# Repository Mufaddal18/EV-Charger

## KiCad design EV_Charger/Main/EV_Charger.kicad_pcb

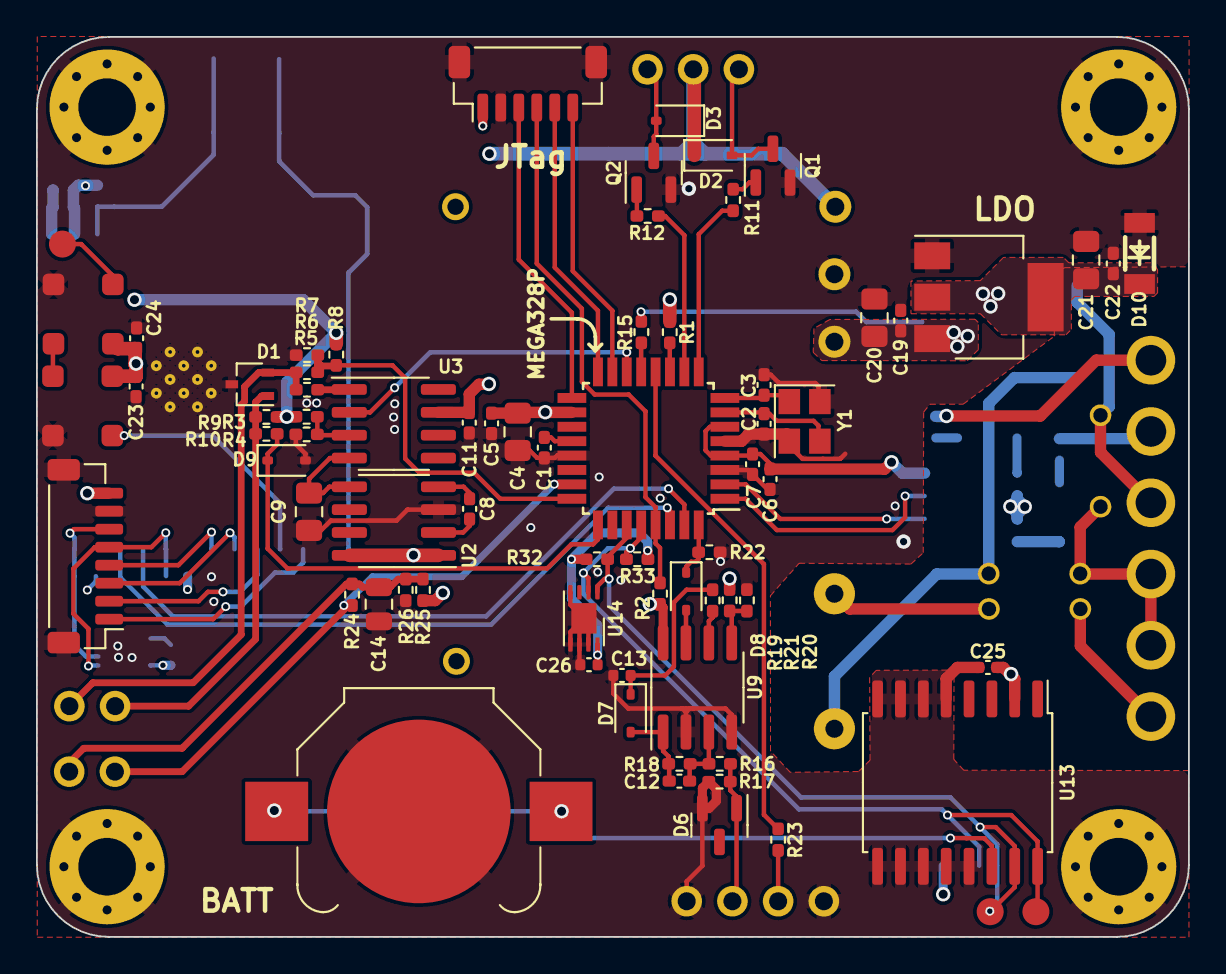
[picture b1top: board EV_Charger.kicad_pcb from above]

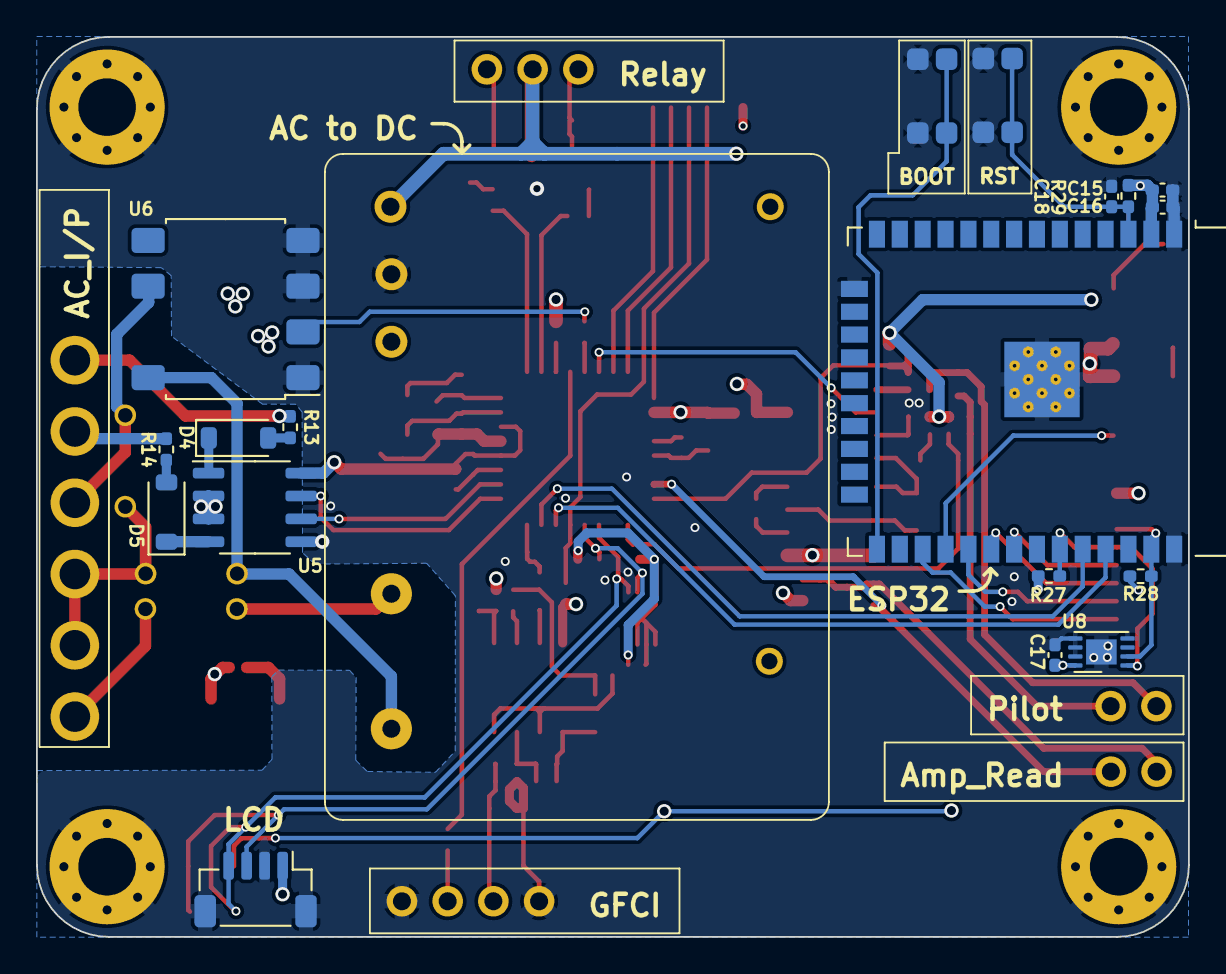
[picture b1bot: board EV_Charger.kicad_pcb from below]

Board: 4 copper layers, 64.0 x 50.0 mm, 104 parts (22 on the bottom side), 71 nets.

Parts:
BT1: Cell; BatteryHolder_Keystone_3000_1x12mm
C1, C5, C6, C7, C11, C12, C17, C19, C22, C23, C24: 100nF; C_0402_1005Metric_Pad0.74x0.62mm_HandSolder
C2, C3: 10pF; C_0402_1005Metric_Pad0.74x0.62mm_HandSolder
C4, C9, C20, C21: 10uF; C_0805_2012Metric_Pad1.18x1.45mm_HandSolder
C8, C15: 10uF; C_0402_1005Metric_Pad0.74x0.62mm_HandSolder
C13: 10uF; C_0402_1005Metric
C14: 100nF; C_0805_2012Metric
C16, C18: 1uF; C_0402_1005Metric_Pad0.74x0.62mm_HandSolder
C25, C26: 100nF; C_0402_1005Metric
D1: ESDA25W; SOT-323_SC-70
D2, D3, D7, D8, D9: 1N4148WS; D_SOD-323
D4, D5: PMEG40T30ERX; D_SOD-123
D6: BAS40-06; SOT-23
D10: Zener; LL-34_L3.5-W1.5-RD
F1, F2: RST1.6AMMO; General
H1, H2, H3, H4: MountingHole_Pad; MountingHole_3.2mm_M3_Pad_Via
J1: Pilot; PinHeader_1x02_P2.54mm_Vertical
J2: DC_Relay; PinHeader_1x03_P2.54mm_Vertical
J3: AC IN; JST_VH_B6P-VH-B_1x06_P3.96mm_Vertical
J4: GFCI; PinHeader_1x04_P2.54mm_Vertical
J5: AMP_Read; PinHeader_1x02_P2.54mm_Vertical
J6: Conn_01x08; JST_SH_BM08B-SRSS-TB_1x08-1MP_P1.00mm_Vertical
J7: LCD; JST_SH_BM04B-SRSS-TB_1x04-1MP_P1.00mm_Vertical
J8: JTAG; JST_SH_BM06B-SRSS-TB_1x06-1MP_P1.00mm_Vertical
LED_O1: LED_O; TestPoint_Pad_D1.5mm
Q1, Q2: BCX70G; SOT-23
R1, R2, R11, R12, R15, R23: 330R; R_0402_1005Metric_Pad0.72x0.64mm_HandSolder
R3, R4, R7, R18, R21, R25, R26: 100K; R_0402_1005Metric_Pad0.72x0.64mm_HandSolder
R5: 620R; R_0402_1005Metric_Pad0.72x0.64mm_HandSolder
R6, R10: 200K; R_0402_1005Metric_Pad0.72x0.64mm_HandSolder
R8: 56K; R_0402_1005Metric_Pad0.72x0.64mm_HandSolder
R9, R16: 1K; R_0402_1005Metric_Pad0.72x0.64mm_HandSolder
R13, R14: 330K; R_0402_1005Metric_Pad0.72x0.64mm_HandSolder
R17: 412R; R_0402_1005Metric_Pad0.72x0.64mm_HandSolder
R19: 100R; R_0402_1005Metric_Pad0.72x0.64mm_HandSolder
R20: 20K; R_0402_1005Metric_Pad0.72x0.64mm_HandSolder
R22, R29: 10K; R_0402_1005Metric_Pad0.72x0.64mm_HandSolder
R24: 22R; R_0402_1005Metric_Pad0.72x0.64mm_HandSolder
R27, R28, R32, R33: 4.7K; R_0402_1005Metric_Pad0.72x0.64mm_HandSolder
RV1: V250LA10P; General
SW1, SW2: KMR211GLFS; Switch
TP2: T_SCL; TestPoint_Pad_D1.5mm
TP3: T_SDA; TestPoint_Pad_D1.5mm
U1: ATmega328P; TQFP-32_7x7mm_P0.8mm
U2: TC1044S; SOIC-8_3.9x4.9mm_P1.27mm
U3, U9: LM358; SOIC-8_3.9x4.9mm_P1.27mm
U4: MPM-04E-1205
U5: HCPL-2731-300E; SO-8_3.9x4.9mm_P1.27mm
U6: AQH1213A; SSO-7-8_6.4x9.78mm_P2.54mm
U7: ESP32-WROOM-32
U8, U14: MCP9808; DFN-8-1EP_3x2mm_P0.5mm_EP1.7x1.4mm
U10: LM1117; SOT-223-3_TabPin2
U11, U12: COM-16347
U13: DS3231SN; SOIC-16W_7.5x10.3mm_P1.27mm
Y1: 16Mhz; Crystal_SMD_3225-4Pin_3.2x2.5mm

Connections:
+3V3: C15.1, C16.1, C17.1, C21.1, C22.1, C26.1, D10.1 (K), J6.8, R27.1, R28.1, R29.1, R32.1, R33.1, U7.2 (VDD), U8.8 (V_{DD}), U10.2 (VO), U14.8 (V_{DD})
+5V: C4.1, C5.1, C6.1, C7.1, C19.1, C20.1, C23.1, C24.1, C25.1, J7.1, J8.1, R1.2, R2.2, R3.2, R8.1, R9.2, R21.2, R25.2, U1.4 (VCC), U1.6 (VCC), U1.18 (AVCC), U4.5, U5.8 (VCC), U9.8 (V+), U10.3 (VI), U11.1 (VI), U12.1 (VI), U13.2 (VCC)
+12V: C11.2, D2.1 (K), D3.1 (K), J2.2, U2.1 (BOOST), U2.8 (V+), U3.7 (V+), U4.3
/Main_Board/FUSEL: F2.2, U4.7 (Pin_6), U6.8
/Main_Board/FUSEN: F1.2, U4.6
/Main_Board/JT_MISO: J8.5, U1.16 (PB4)
/Main_Board/JT_MOSI: J8.6, U1.15 (PB3)
/Main_Board/JT_NRST: J8.4, R2.1, U1.29 (~RESET/PC6)
/Main_Board/JT_SCK: J8.3, U1.17 (PB5)
AC_IN1: F1.1, J3.1
AC_IN2: F2.1, J3.2, J3.3, RV1.2
AC_RELAY: J3.4, RV1.1, U6.6
AC_RELAY1: R15.1, U1.13 (PB1)
AC_TEST1: J3.6, R13.1
AC_TEST2: J3.5, R14.1
AC_TEST_O1: U1.1 (PD3), U5.7 (VO1)
AC_TEST_O2: U1.2 (PD4), U5.6 (VO2)
AMP_READ: J5.1, R24.2, U1.23 (PC0)
DC_REALY1: R11.2, U1.9 (PD5)
DC_REALY2: R12.2, U1.10 (PD6)
ESP_RESET: C18.1, R29.2, SW2.1, SW2.4, U7.3 (EN)
GFCI_INT: D8.1 (K), R22.2, U1.32 (PD2)
GFCI_TEST: R23.2, U1.12 (PB0)
GND: BT1.2 (-), C1.2, C2.2, C3.1, C4.2, C5.2, C6.2, C7.2, C9.1, C11.1, C13.1, C14.1, C15.2, C16.2, C17.2, C18.2, C19.2, C20.2, C21.2, C22.2, C23.2, C24.2, C25.2, C26.2, D1.3 (VN), D6.2, D9.2 (A), D10.2 (A), H1.1, H2.1, H3.1, H4.1, J4.1, J4.4, J6.7, J7.2, J8.2, Q1.2 (E), Q2.2 (E), R4.1, R7.2, R17.1, R20.1, R22.1, R26.1, SW1.2, SW1.3, SW2.2, SW2.3, U1.3 (GND), U1.5 (GND), U1.21 (GND), U2.3 (GND), U4.4, U5.2 (C1), U5.3 (C2), U5.5 (GND), U6.1, U6.3, U6.4, U7.1 (GND), U7.15 (GND), U7.38 (GND), U7.39 (GND), U8.4 (GND), U8.5 (A2), U8.6 (A1), U8.7 (A0), U8.9 (EP/GND), U9.2 (-), U9.4 (V-), U10.1 (GND), U11.3 (GND), U12.3 (GND), U13.5 (GND), U13.6 (GND), U13.7 (GND), U13.8 (GND), U13.9 (GND), U13.10 (GND), U13.11 (GND), U13.12 (GND), U13.13 (GND), U14.4 (GND), U14.5 (A2), U14.6 (A1), U14.7 (A0), U14.9 (EP/GND), Y1.2, Y1.4
GPIO0: SW1.1, SW1.4, U7.25 (IO0)
IO16: J6.1, U7.27 (IO16)
LCD_SCL: J7.3, R33.2, TP2.1, U1.28 (PC5), U13.16 (SCL), U14.2 (SCL)
LCD_SDA: J7.4, R32.2, TP3.1, U1.27 (PC4), U13.15 (SDA), U14.1 (SDA)
LED: U7.28 (IO17), U11.4 (DIN)
MISO: J6.4, U7.31 (IO19)
MOSI: J6.3, U7.30 (IO18)
unnamed: BT1.1 (+), U13.14 (VBAT)
unnamed: D2.2 (A), J2.1, Q1.3 (C)
unnamed: D3.2 (A), J2.3, Q2.3 (C)
unnamed: D4.2 (A), R13.2
unnamed: D4.1 (K), U5.1 (A1)
unnamed: D5.2 (A), R14.2
unnamed: D5.1 (K), U5.4 (A2)
unnamed: C12.2, D7.2 (A), R18.2, U9.1
unnamed: C13.2, D7.1 (K), R19.1
unnamed: D8.2 (A), U9.7
unnamed: D6.1, J4.2, R16.1, R17.2
unnamed: J4.3, R23.1
unnamed: C14.2, J5.2, R24.1, R25.1, R26.2
unnamed: Q1.1 (B), R11.1
unnamed: Q2.1 (B), R12.1
unnamed: R5.2, U3.1
unnamed: R15.2, U6.2
unnamed: C1.1, U1.20 (AREF)
unnamed: R1.1, U1.11 (PD7)
unnamed: C2.1, U1.7 (XTAL1/PB6), Y1.3
unnamed: C3.2, U1.8 (XTAL2/PB7), Y1.1
unnamed: C8.2, U2.2 (CAP+)
unnamed: C8.1, U2.4 (CAP-)
unnamed: C9.2, U2.5 (VOUT), U3.4 (V-)
unnamed: R3.1, R4.2, U3.3 (+)
unnamed: C12.1, R16.2, R18.1, U9.3 (+)
unnamed: R20.2, R21.1, U9.5 (+)
unnamed: R19.2, U9.6 (-)
unnamed: U11.2 (VO), U12.4 (DIN)
unnamed: LED_O1.1, U12.2 (VO)
PILOT_READ: R6.2, R7.1, R8.2, U1.24 (PC1)
PP: D1.1 (CH1), J1.2, R9.1, R10.2
PP_READ: D9.1 (K), R10.1, U1.25 (PC2)
PWM: U1.14 (PB2), U3.2 (-)
Pilot: D1.2 (VP), J1.1, R5.1, R6.1
SCK: J6.2, U7.29 (IO5)
SCL: J6.6, R28.2, U7.37 (IO23), U8.2 (SCL)
SDA: J6.5, R27.2, U7.33 (IO21), U8.1 (SDA)
Wifi_RX: U1.30 (PD0), U7.35 (TXD0/IO1)
Wifi_TX: U1.31 (PD1), U7.34 (RXD0/IO3)

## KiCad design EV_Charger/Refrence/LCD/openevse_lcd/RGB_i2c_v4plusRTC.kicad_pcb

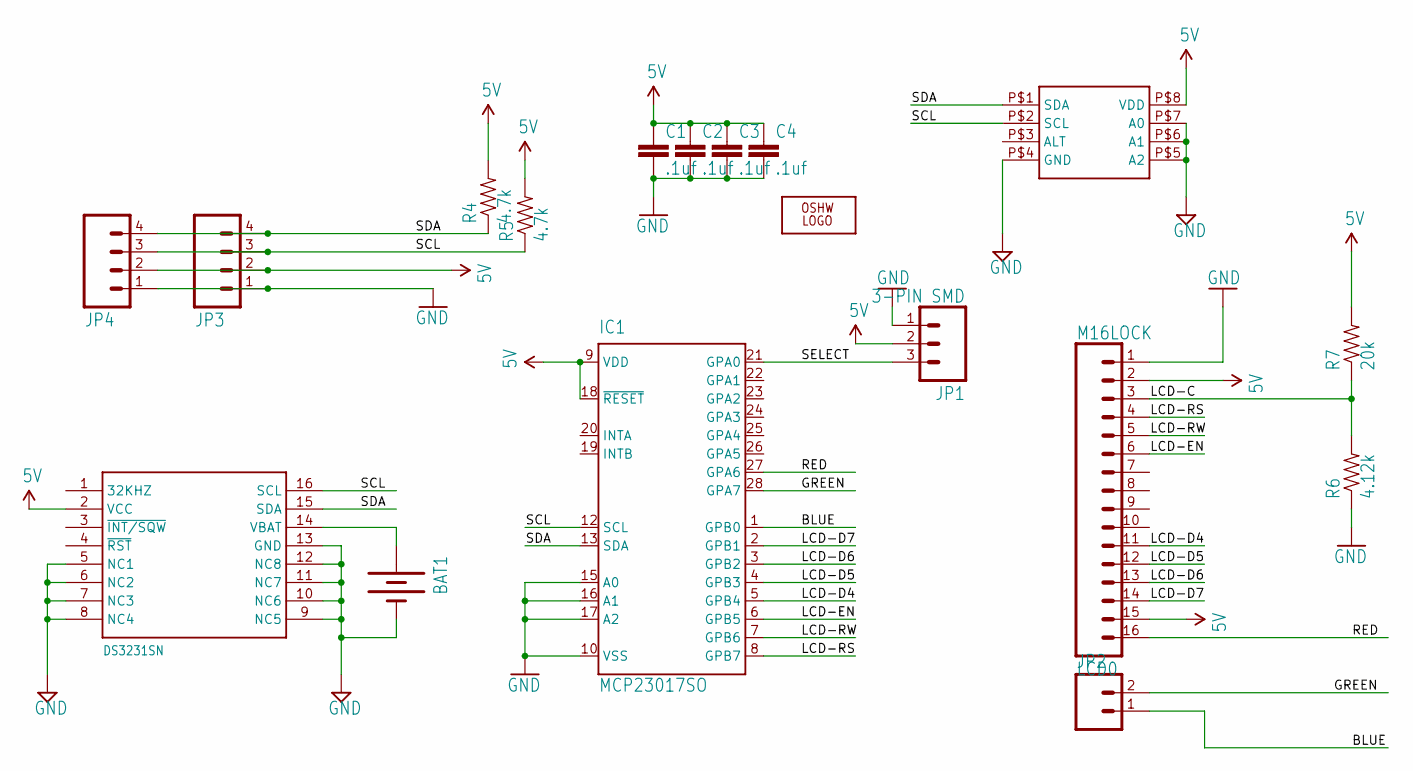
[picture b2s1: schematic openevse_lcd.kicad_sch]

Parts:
BAT1: BATTERY12MM; BATTCON_12MM
C1, C2, C3, C4: .1uf; 0805
IC1: MCP23017SO; SO28W
IC2: DS3231SN; SO16W
IC3: MCP9808; MSOP8
JP1: 3-PIN SMD; JST-3-SMD
JP2: M02PTH; 1X02
JP3, JP4: M04JST-PTH-VERT; JST-4-PTH-VERT
LCD0: M16LOCK; 1X16_LOCK
LOGO2: OSHW_LOGO_10MILX0350-NT; OSHW_10X350_NOTEXT
R4, R5: 4.7k; 0805
R6: 4.12k; 0805
R7: 20k; 0805

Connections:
5V: C1.1, C2.1, C3.1, C4.1, IC1.9 (VDD), IC1.18 (~RESET), IC2.2 (VCC), IC3.P$8 (VDD), JP1.2, JP3.2 (3), JP4.2 (3), LCD0.2, LCD0.15, R4.2, R5.2, R7.2
BLUE: IC1.1 (GPB0), JP2.1
GND: BAT1.GND (-), C1.2, C2.2, C3.2, C4.2, IC1.10 (VSS), IC1.15 (A0), IC1.16 (A1), IC1.17 (A2), IC2.5 (NC1), IC2.6 (NC2), IC2.7 (NC3), IC2.8 (NC4), IC2.9 (NC5), IC2.10 (NC6), IC2.11 (NC7), IC2.12 (NC8), IC2.13 (GND), IC3.P$4 (GND), IC3.P$5 (A2), IC3.P$6 (A1), IC3.P$7 (A0), JP1.1, JP3.1 (4), JP4.1 (4), LCD0.1, R6.1
GREEN: IC1.28 (GPA7), JP2.2
LCD-C: LCD0.3, R6.2, R7.1
LCD-D4: IC1.5 (GPB4), LCD0.11
LCD-D5: IC1.4 (GPB3), LCD0.12
LCD-D6: IC1.3 (GPB2), LCD0.13
LCD-D7: IC1.2 (GPB1), LCD0.14
LCD-EN: IC1.6 (GPB5), LCD0.6
LCD-RS: IC1.8 (GPB7), LCD0.4
LCD-RW: IC1.7 (GPB6), LCD0.5
unnamed: BAT1.PWR@1 (+), IC2.14 (VBAT)
RED: IC1.27 (GPA6), LCD0.16
SCL: IC1.12 (SCL), IC2.16 (SCL), IC3.P$2 (SCL), JP3.3 (2), JP4.3 (2), R5.1
SDA: IC1.13 (SDA), IC2.15 (SDA), IC3.P$1 (SDA), JP3.4 (1), JP4.4 (1), R4.1
SELECT: IC1.21 (GPA0), JP1.3

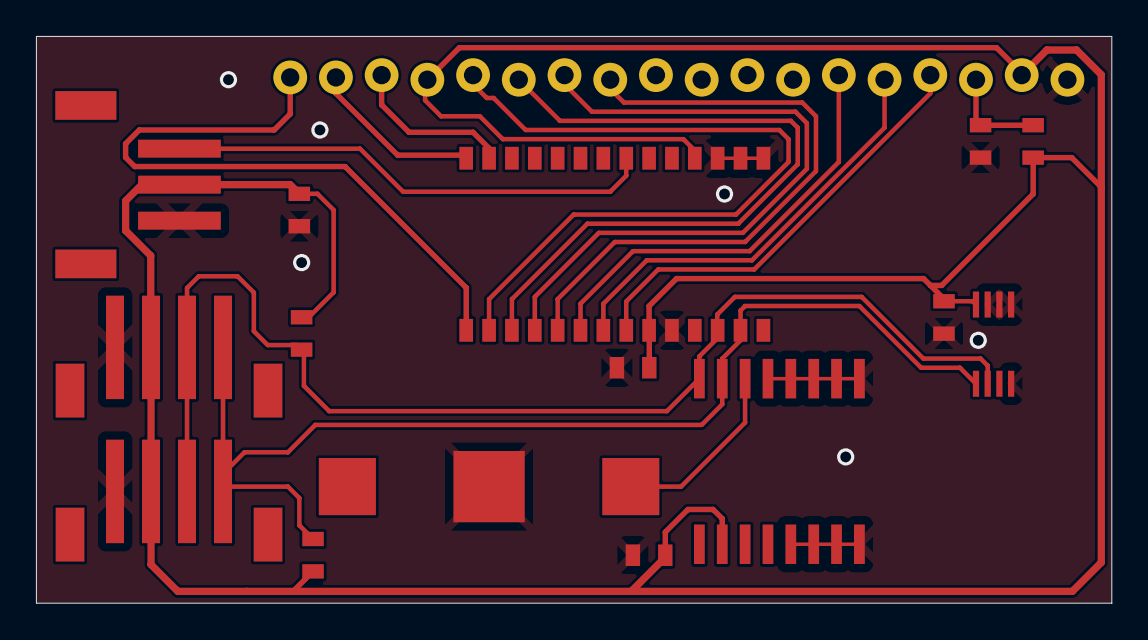
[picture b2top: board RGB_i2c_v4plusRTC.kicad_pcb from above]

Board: 2 copper layers, 59.7 x 31.5 mm, 18 parts (0 on the bottom side), 17 nets.

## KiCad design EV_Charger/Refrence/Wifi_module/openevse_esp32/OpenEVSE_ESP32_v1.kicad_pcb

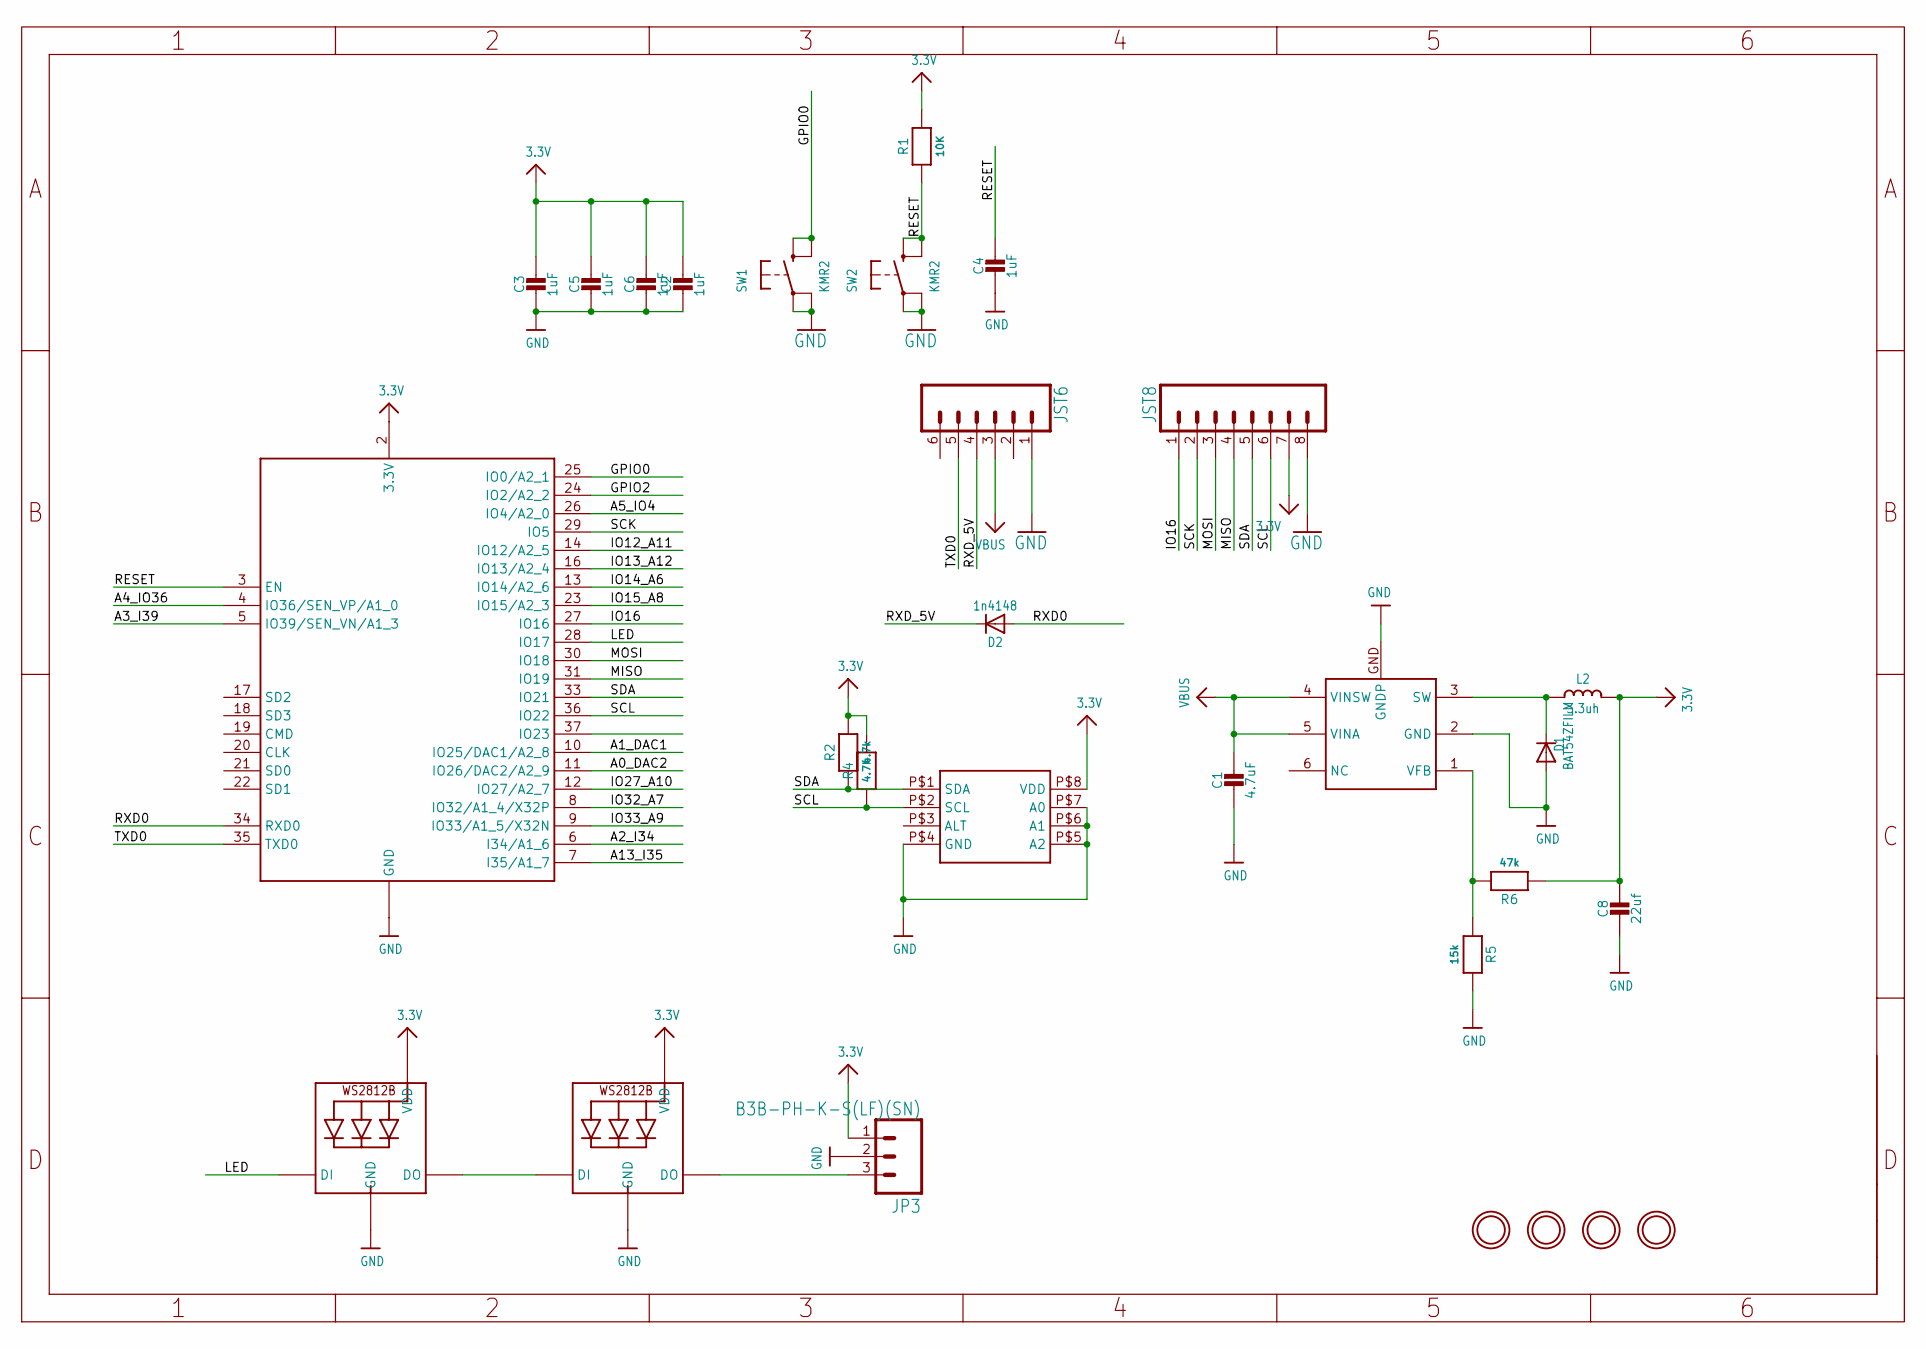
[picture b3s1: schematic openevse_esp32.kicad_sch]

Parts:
C1: 4.7uF; 0603-NO
C2, C3, C4, C5, C6: 1uF; 0603-NO
C8: 22uf; 0603-NO
D1: BAT54ZFILM; SOD-123
D2: 1n4148; SOD-323
IC1: ST1S03; DFQN6D
IC2: MCP9808; MSOP8
JP1: JST6
JP2: JST8
JP3: B3B-PH-K-S(LF)(SN); JST-3-PTH-VERT
L2: 3.3uh; MICROBUILDER_INDUCTOR_5X5MM_NR5040_NOTHERMALS
LED1, LED2: MICROBUILDER_WS2812B3535; MICROBUILDER_LED3535
R1: 10K; 0603-NO
R2, R4: 4.7k; 0603-NO
R5: 15k; 0603-NO
R6: 47k; 0603-NO
SW1, SW2: KMR2; BTN_KMR2_4.6X2.8
U$8, U$17, U$25, U$27: MOUNTINGHOLE2.5; MOUNTINGHOLE_2.5_PLATED
X2: ESP32_WROOM32_SKINNY; WROOM32_SKINNY

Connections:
3.3V: C2.1, C3.1, C5.1, C6.1, C8.1, IC2.P$8 (VDD), JP2.7, JP3.1, L2.P$2 (2), LED1.2 (VDD), LED2.2 (VDD), R1.2, R2.2, R4.2, R6.1, X2.2 (3.3V)
A0_DAC2: X2.11 (IO26/DAC2/A2_9)
A1_DAC1: X2.10 (IO25/DAC1/A2_8)
A2_I34: X2.6 (I34/A1_6)
A3_I39: X2.5 (IO39/SEN_VN/A1_3)
A4_IO36: X2.4 (IO36/SEN_VP/A1_0)
A5_IO4: X2.26 (IO4/A2_0)
A13_I35: X2.7 (I35/A1_7)
GND: C1.2, C2.2, C3.2, C4.2, C5.2, C6.2, C8.2, D1.A, IC1.2 (GND), IC1.GND (GNDP), IC2.P$4 (GND), IC2.P$5 (A2), IC2.P$6 (A1), IC2.P$7 (A0), JP1.1, JP2.8, JP3.2, LED1.4 (GND), LED2.4 (GND), R5.2, SW1.A, SW1.A' (P1), SW2.A, SW2.A' (P1), X2.1 (GND), X2.15 (GND), X2.38 (GND), X2.P$1 (GND)
GPIO0: SW1.B (S), SW1.B' (S1), X2.25 (IO0/A2_1)
GPIO2: X2.24 (IO2/A2_2)
IO12_A11: X2.14 (IO12/A2_5)
IO13_A12: X2.16 (IO13/A2_4)
IO14_A6: X2.13 (IO14/A2_6)
IO15_A8: X2.23 (IO15/A2_3)
IO16: JP2.1, X2.27 (IO16)
IO27_A10: X2.12 (IO27/A2_7)
IO32_A7: X2.8 (IO32/A1_4/X32P)
IO33_A9: X2.9 (IO33/A1_5/X32N)
LED: LED1.1 (DI), X2.28 (IO17)
MISO: JP2.4, X2.31 (IO19)
MOSI: JP2.3, X2.30 (IO18)
unnamed: JP3.3, LED2.3 (DO)
unnamed: LED1.3 (DO), LED2.1 (DI)
unnamed: IC1.1 (VFB), R5.1, R6.2
unnamed: D1.C, IC1.3 (SW), L2.P$1 (1)
RESET: C4.1, R1.1, SW2.B (S), SW2.B' (S1), X2.3 (EN)
RXD0: D2.A, X2.34 (RXD0)
RXD_5V: D2.C, JP1.4
SCK: JP2.2, X2.29 (IO5)
SCL: IC2.P$2 (SCL), JP2.6, R4.1, X2.36 (IO22)
SDA: IC2.P$1 (SDA), JP2.5, R2.1, X2.33 (IO21)
TXD0: JP1.5, X2.35 (TXD0)
VBUS: C1.1, IC1.4 (VINSW), IC1.5 (VINA), JP1.3

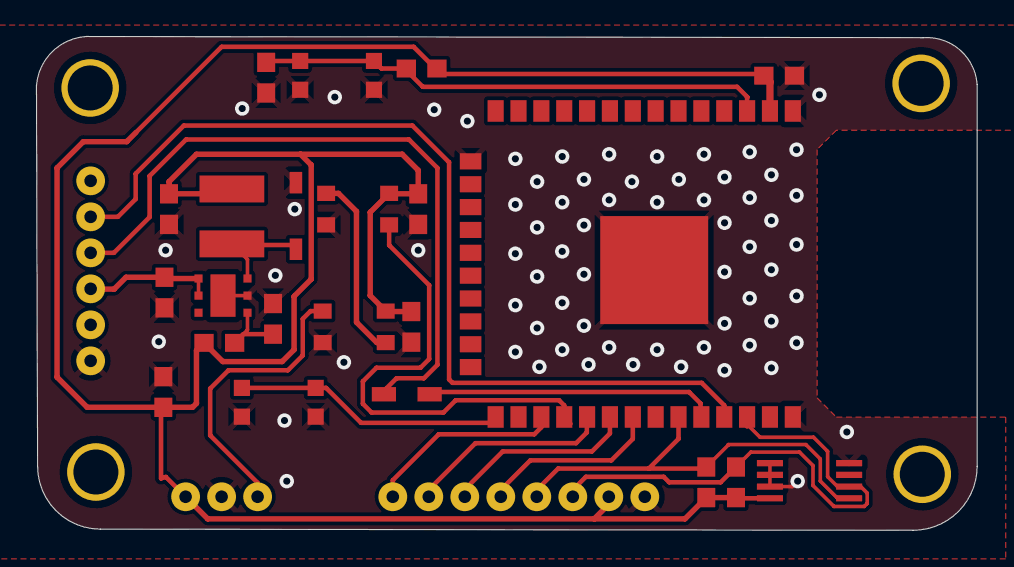
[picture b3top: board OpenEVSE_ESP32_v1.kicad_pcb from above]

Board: 2 copper layers, 52.3 x 27.4 mm, 29 parts (0 on the bottom side), 19 nets.

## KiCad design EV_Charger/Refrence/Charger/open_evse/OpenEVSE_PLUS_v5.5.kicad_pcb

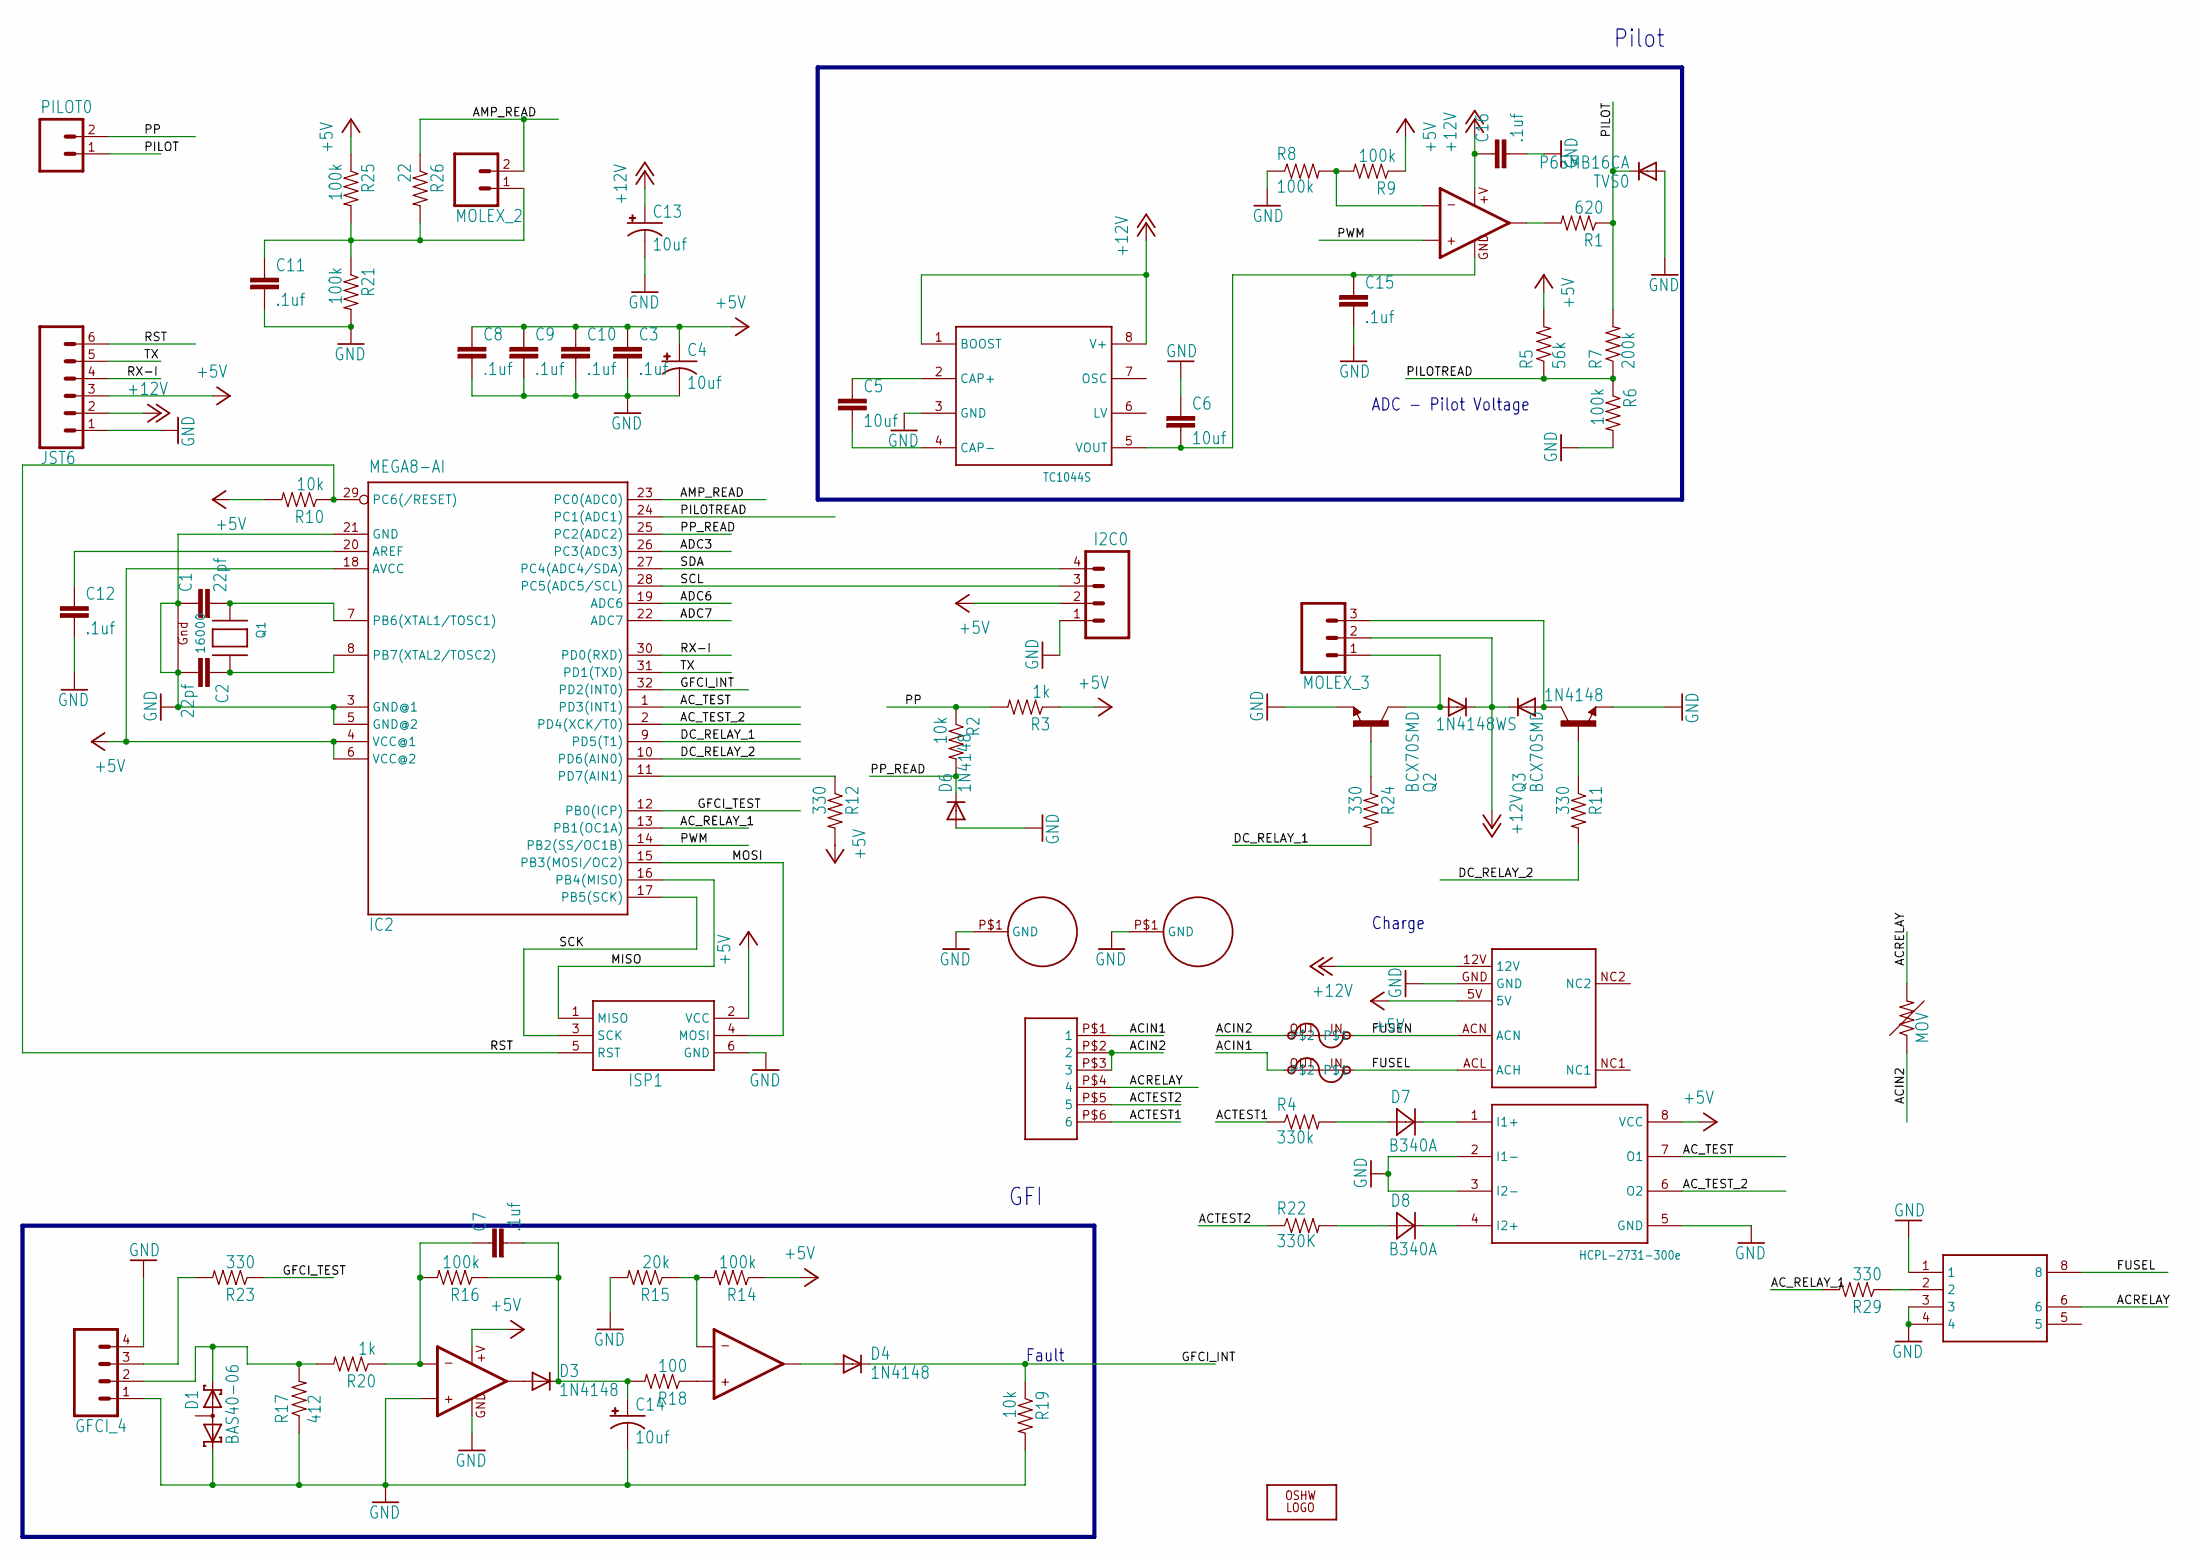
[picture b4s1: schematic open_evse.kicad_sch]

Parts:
AC0: JST-VH-6
AMP_CT0: MOLEX_2
C1, C2: 22pf; 0805
C3, C7, C8, C9, C10, C11, C12, C15, C16: .1uf; 0805
C4, C13, C14: 10uf; EIA3216
C5, C6: 10uf; 1206-CAP
COMM0: JST6
D1: BAS40-06; SOT23
D2, D3, D4, D6: 1N4148; SOD123
D5: 1N4148WS; SOD123
D7, D8: B340A; SMA
DC_RELAY0: MOLEX_3
F1, F2: BEL1AFUSE; BELFUSE1A
GFCI_CT0: GFCI_4
I2C0: M04JST-PTH-VERT; JST-4-PTH-VERT
IC1: HCPL-2731-300e; DIP08
IC2: MEGA8-AI; TQFP32-08
IC3: LMV358; SO08
IC4: lm358w; SO08
IC5: AQH1213; DIP7
IC6: TC1044S; SO-8
ISP1: AVRISP-6; AVRISP
LOGO1: OSHW_LOGO_8MILX0150-NT; OSHW_8X150_NOTEXT
PILOT0: M025MM; SCREWTERMINAL-5MM-2
PS1: MPM-04E-1205
Q1: 16000; NX3225
Q2, Q3: BCX70SMD; SOT23
R1: 620; 0805
R2, R10, R19: 10k; 0805
R3, R20: 1k; 0805
R4: 330k; AXIAL-0.4
R5: 56k; 0805
R6, R8, R9, R14, R16, R21, R25: 100k; 0805
R7: 200k; 0805
R11, R12, R23, R24, R29: 330; 0805
R15: 20k; 0805
R17: 412; 0805
R18: 100; 0805
R22: 330K; AXIAL-0.4
R26: 22; 0805
TVS0: P6SMB16CA; SMB
U$1: MOV
U$3, U$4: HOLE

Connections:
+5V: C3.1, C4.A (+), C8.1, C9.1, C10.1, COMM0.3, I2C0.2, IC1.8 (VCC), IC2.4 (VCC@1), IC2.6 (VCC@2), IC2.18 (AVCC), IC3.8 (+V), ISP1.2 (VCC), PS1.5V, R3.1, R5.2, R9.1, R10.2, R12.2, R14.1, R25.1
+12V: C13.A (+), C16.1, COMM0.2, D2.C, D5.C, DC_RELAY0.2, IC4.8 (+V), IC6.1 (BOOST), IC6.8 (V+), PS1.12V
-12V: C6.2, C15.1, IC4.4 (GND), IC6.5 (VOUT)
ACIN1: AC0.P$1 (1), F2.OUT
ACIN2: AC0.P$2 (2), AC0.P$3 (3), F1.OUT, U$1.P$1 (1)
ACRELAY: AC0.P$4 (4), IC5.6, U$1.P$2 (2)
ACTEST1: AC0.P$6 (6), R4.P$1 (1)
ACTEST2: AC0.P$5 (5), R22.P$1 (1)
AC_RELAY_1: IC2.13 (PB1(OC1A)), R29.2
AC_TEST: IC1.7 (O1), IC2.1 (PD3(INT1))
AC_TEST_2: IC1.6 (O2), IC2.2 (PD4(XCK/T0))
ADC3: IC2.26 (PC3(ADC3))
ADC6: IC2.19 (ADC6)
ADC7: IC2.22 (ADC7)
AMP_READ: AMP_CT0.2, IC2.23 (PC0(ADC0)), R26.1
DC_RELAY_1: IC2.9 (PD5(T1)), R24.2
DC_RELAY_2: IC2.10 (PD6(AIN0)), R11.2
FUSEL: F2.IN, IC5.8, PS1.ACL (ACH)
FUSEN: F1.IN, PS1.ACN
GFCI_INT: D4.C, IC2.32 (PD2(INT0)), R19.1
GFCI_TEST: IC2.12 (PB0(ICP)), R23.1
GND: C1.1, C2.2, C3.2, C4.C (-), C6.1, C8.2, C9.2, C10.2, C11.2, C12.2, C13.C (-), C14.C (-), C15.2, C16.2, COMM0.1, D1.1 (K1), D6.A, GFCI_CT0.1, GFCI_CT0.4, I2C0.1, IC1.2 (I1-), IC1.3 (I2-), IC1.5 (GND), IC2.3 (GND@1), IC2.5 (GND@2), IC2.21 (GND), IC3.3 (+IN1), IC3.4 (GND), IC5.1, IC5.3, IC5.4, IC6.3 (GND), ISP1.6 (GND), PS1.GND, Q1.1 (G1), Q1.3 (G2), Q2.2 (E), Q3.2 (E), R6.2, R8.1, R15.2, R17.1, R19.2, R21.2, TVS0.A, U$3.P$1, U$4.P$1
MISO: IC2.16 (PB4(MISO)), ISP1.1 (MISO)
MOSI: IC2.15 (PB3(MOSI/OC2)), ISP1.4 (MOSI)
unnamed: D2.A, DC_RELAY0.3, Q3.3 (C)
unnamed: Q3.1 (B), R11.1
unnamed: C1.2, IC2.7 (PB6(XTAL1/TOSC1)), Q1.2 (X1)
unnamed: C2.1, IC2.8 (PB7(XTAL2/TOSC2)), Q1.4 (X2)
unnamed: D5.A, DC_RELAY0.1, Q2.3 (C)
unnamed: AMP_CT0.1, C11.1, R21.1, R25.2, R26.2
unnamed: C7.1, IC3.2 (-IN1), R16.2, R20.1
unnamed: D7.A, R4.P$2 (2)
unnamed: IC4.2 (-IN1), R8.2, R9.2
unnamed: IC4.1 (OUT1), R1.2
unnamed: D7.C, IC1.1 (I1+)
unnamed: D8.C, IC1.4 (I2+)
unnamed: D8.A, R22.P$2 (2)
unnamed: IC5.2, R29.1
unnamed: C5.1, IC6.2 (CAP+)
unnamed: D1.2 (K2), GFCI_CT0.2, R17.2, R20.2
unnamed: D3.A, IC3.1 (OUT1)
unnamed: GFCI_CT0.3, R23.2
unnamed: C7.2, C14.A (+), D3.C, R16.1, R18.2
unnamed: IC3.6 (-IN2), R14.2, R15.1
unnamed: D4.A, IC3.7 (OUT2)
unnamed: IC3.5 (+IN2), R18.1
unnamed: C5.2, IC6.4 (CAP-)
unnamed: IC2.11 (PD7(AIN1)), R12.1
unnamed: Q2.1 (B), R24.1
unnamed: C12.1, IC2.20 (AREF)
PILOT: PILOT0.1, R1.1, R7.2, TVS0.C
PILOTREAD: IC2.24 (PC1(ADC1)), R5.1, R6.1, R7.1
PP: PILOT0.2, R2.1, R3.2
PP_READ: D6.C, IC2.25 (PC2(ADC2)), R2.2
PWM: IC2.14 (PB2(SS/OC1B)), IC4.3 (+IN1)
RST: COMM0.6, IC2.29 (PC6(/RESET)), ISP1.5 (RST), R10.1
RX-I: COMM0.4, IC2.30 (PD0(RXD))
SCK: IC2.17 (PB5(SCK)), ISP1.3 (SCK)
SCL: I2C0.3, IC2.28 (PC5(ADC5/SCL))
SDA: I2C0.4, IC2.27 (PC4(ADC4/SDA))
TX: COMM0.5, IC2.31 (PD1(TXD))

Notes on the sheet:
Charge
Fault
ADC - Pilot Voltage
Pilot
GFI

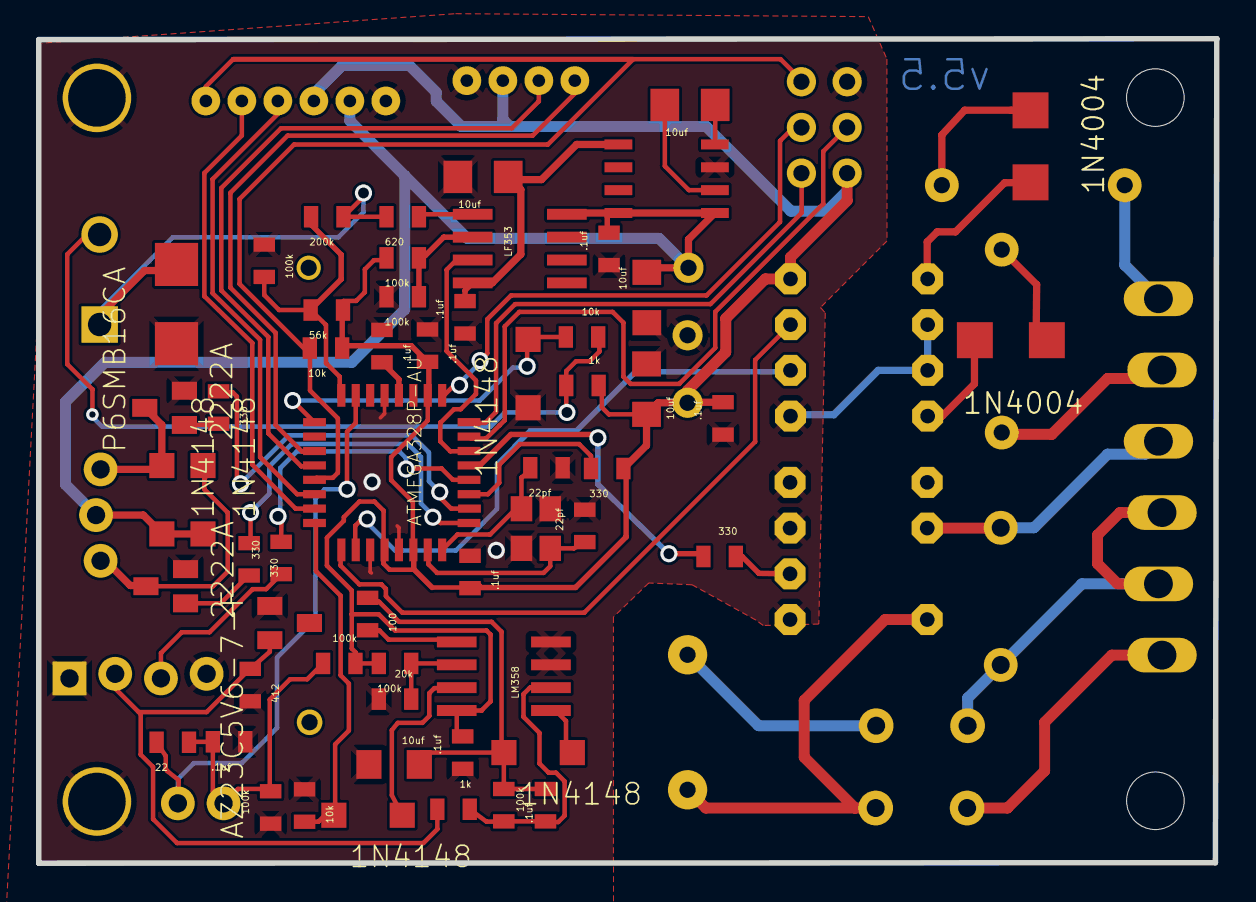
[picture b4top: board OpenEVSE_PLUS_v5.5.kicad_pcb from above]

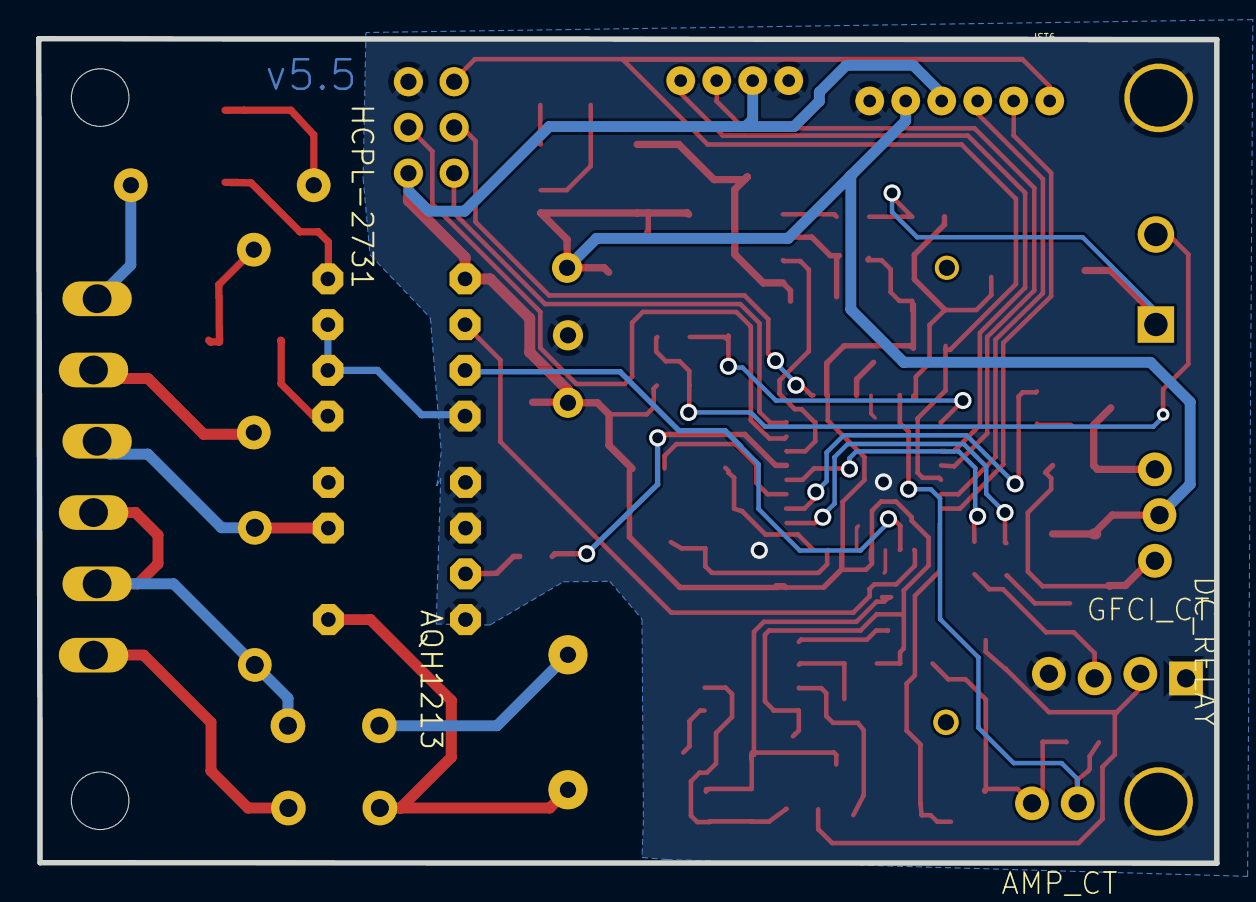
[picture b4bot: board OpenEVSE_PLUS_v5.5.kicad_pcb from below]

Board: 2 copper layers, 65.4 x 45.8 mm, 78 parts (17 on the bottom side), 58 nets.

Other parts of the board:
@HOLE0, @HOLE1: (no value)
LOGO2: OSHW_LOGO_8MILX0150-NT; OSHW_8X150_NOTEXT
